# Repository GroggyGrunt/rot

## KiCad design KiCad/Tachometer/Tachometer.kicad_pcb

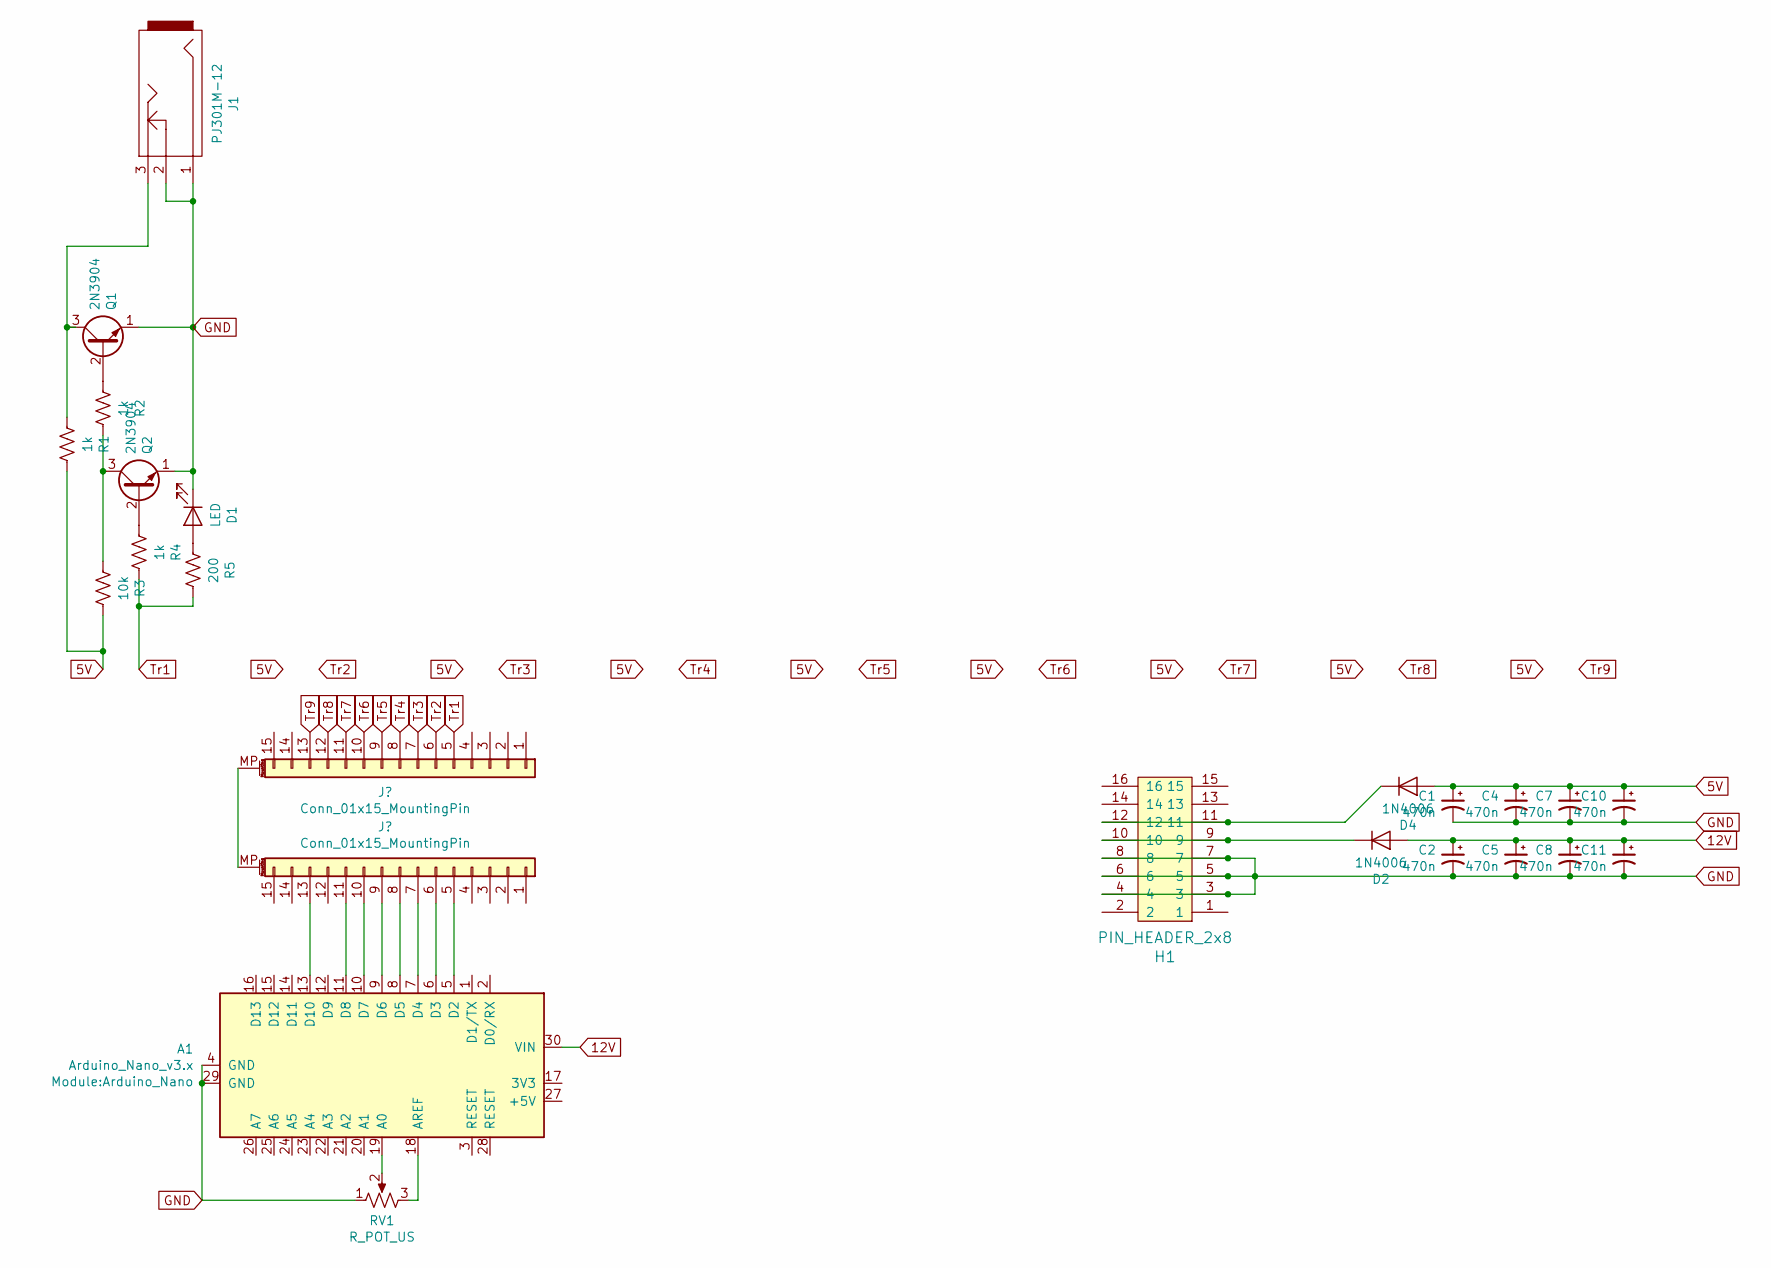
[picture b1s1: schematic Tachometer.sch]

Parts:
A1: Arduino_Nano_v3.x; Arduino_Nano
C1, C2, C4, C5, C7, C8, C10, C11: 470n; C_1206_3216Metric_Pad1.42x1.75mm_HandSolder
D1: LED; LED_D3.0mm_FlatTop
D2, D4: 1N4006; D_DO-41_SOD81_P7.62mm_Horizontal
H1: PIN_HEADER_2x8; PinHeader_2x08_P2.54mm_Vertical
J1: PJ301M-12
Q1, Q2: 2N3904; SOT-23-3
R1, R2, R4: 1k; R_1206_3216Metric_Pad1.42x1.75mm_HandSolder
R3: 10k; R_1206_3216Metric_Pad1.42x1.75mm_HandSolder
R5: 200; R_1206_3216Metric_Pad1.42x1.75mm_HandSolder
RV1: R_POT_US; Alpha9mmPot

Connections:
5V: C1.1, C4.1, C7.1, C10.1, D4.2 (A), R1.1, R3.1
12V: A1.30 (VIN), C2.1, C5.1, C8.1, C11.1, D2.2 (A)
GND: A1.4 (GND), A1.29 (GND), C1.2, C2.2, C4.2, C5.2, C7.2, C8.2, C10.2, C11.2, D1.1 (K), H1.3, H1.4, H1.5, H1.6, H1.7, H1.8, J1.1, J1.2, Q1.1 (E), Q2.1 (E), RV1.1
unnamed 6: A1.5 (D2); also elsewhere on the board
unnamed 7: A1.6 (D3); also elsewhere on the board
unnamed 8: A1.7 (D4); also elsewhere on the board
unnamed 9: A1.8 (D5); also elsewhere on the board
unnamed 10: A1.9 (D6); also elsewhere on the board
unnamed 11: A1.10 (D7); also elsewhere on the board
unnamed 12: A1.11 (D8); also elsewhere on the board
unnamed 14: A1.13 (D10); also elsewhere on the board
unnamed: A1.18 (AREF), RV1.3
unnamed: A1.19 (A0), RV1.2
unnamed: D1.2 (A), R5.2
unnamed: D2.1 (K), H1.9, H1.10
unnamed: D4.1 (K), H1.11, H1.12
unnamed: J1.3, Q1.3 (C), R1.2
unnamed: Q1.2 (B), R2.2
unnamed: Q2.2 (B), R4.2
unnamed: Q2.3 (C), R2.1, R3.2
Tr1: R4.1, R5.1; also elsewhere on the board

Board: 2 copper layers, 24 parts (3 on the bottom side), 21 nets, no tracks yet.

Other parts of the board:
J2, J3: Conn_01x15_MountingPin; PinHeader_1x15_P2.54mm_Vertical

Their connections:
unnamed 6: J3.5; also elsewhere on the board
unnamed 7: J3.6; also elsewhere on the board
unnamed 8: J3.7; also elsewhere on the board
unnamed 9: J3.8; also elsewhere on the board
unnamed 10: J3.9; also elsewhere on the board
unnamed 11: J3.10; also elsewhere on the board
unnamed 12: J3.11; also elsewhere on the board
unnamed 14: J3.13; also elsewhere on the board
Tr1: J2.5; also elsewhere on the board

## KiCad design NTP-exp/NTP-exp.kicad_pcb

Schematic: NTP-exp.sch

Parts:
D1, D3: LED; LED_D3.0mm_FlatTop
D2: CC56-12CGKWA; AFF_2x7SEG-DIGIT_10mm
H1: Expander; PinHeader_2x08_P2.54mm_Vertical
J1, J2, J3, J4, J5, J6, J7, J8, J9, J10, J11, J12, J13, J14: PJ301M-12
R1, R14: 1k; R_0805_2012Metric_Pad1.15x1.40mm_HandSolder
R2, R15: 10m; R_0805_2012Metric_Pad1.15x1.40mm_HandSolder
R3, R4, R5, R6, R11, R12, R13, R16, R17, R18, R19, R20, R21, R22: 51; R_0805_2012Metric_Pad1.15x1.40mm_HandSolder
R7, R8, R9, R10: 200; R_0805_2012Metric_Pad1.15x1.40mm_HandSolder
SW1, SW2: SW_Rotary12
U1, U3, U4, U5: TL074; DIP-14_W7.62mm_Socket
U2: ATmega328P-PU; DIP-28_W7.62mm_Socket

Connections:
5V: H1.15, H1.16, U1.4 (V+), U2.7 (VCC), U2.20 (AVCC), U3.4 (V+), U4.4 (V+), U5.4 (V+)
C1: R7.1, U2.11 (PD5)
C2: R8.1, U2.6 (PD4)
C3: R9.1, U2.5 (PD3)
C4: R10.1, U2.4 (PD2)
GND: H1.13, H1.14, J1.1, J1.2, J2.1, J2.2, J3.1, J3.2, J4.1, J4.2, J5.1, J5.2, J6.1, J6.2, J7.1, J7.2, J8.1, J8.2, J9.1, J9.2, J10.1, J10.2, J11.1, J11.2, J12.1, J12.2, J13.1, J13.2, J14.1, J14.2, R1.2, R2.2, R14.2, R15.2, U1.11 (V-), U2.8 (GND), U2.22 (GND), U3.11 (V-), U4.11 (V-), U5.11 (V-)
La: D2.11 (a), U2.12 (PD6)
Lb: D2.7 (b), U2.13 (PD7)
Lc: D2.4 (c), U2.14 (PB0)
Ld: D2.2 (d), U2.15 (PB1)
Le: D2.1 (e), U2.16 (PB2)
Lf: D2.10 (f), U2.17 (PB3)
Lg: D2.5 (g), U2.18 (PB4)
unnamed: D1.1 (K), R1.1, U1.2 (-)
unnamed: D1.2 (A), U1.1
unnamed: D2.6 (CC4), R10.2
unnamed: D2.8 (CC3), R9.2
unnamed: D2.9 (CC2), R8.2
unnamed: D2.12 (CC1), R7.2
unnamed: D3.1 (K), R14.1, U4.2 (-)
unnamed: D3.2 (A), U4.1
unnamed: J1.3, R3.2
unnamed: J2.3, R4.2
unnamed: J3.3, R5.2
unnamed: J4.3, R6.2
unnamed: J5.3, R11.2
unnamed: J6.3, R12.2
unnamed: J7.3, R13.2
unnamed: J8.3, R16.2
unnamed: J9.3, R17.2
unnamed: J10.3, R18.2
unnamed: J11.3, R19.2
unnamed: J12.3, R20.2
unnamed: J13.3, R21.2
unnamed: J14.3, R22.2
unnamed: R3.1, U1.6 (-), U1.7
unnamed: R4.1, U1.8, U1.9 (-)
unnamed: R5.1, U1.13 (-), U1.14
unnamed: R6.1, U3.1, U3.2 (-)
unnamed: R11.1, U3.6 (-), U3.7
unnamed: R12.1, U3.8, U3.9 (-)
unnamed: R13.1, U3.13 (-), U3.14
unnamed: R16.1, U4.6 (-), U4.7
unnamed: R17.1, U4.8, U4.9 (-)
unnamed: R18.1, U4.13 (-), U4.14
unnamed: R19.1, U5.1, U5.2 (-)
unnamed: R20.1, U5.6 (-), U5.7
unnamed: R21.1, U5.8, U5.9 (-)
unnamed: R22.1, U5.13 (-), U5.14
SDA: H1.11, U2.27 (PC4)
SDC: H1.12, U2.28 (PC5)
STr1: R2.1, R15.1, U1.3 (+), U1.5 (+), U1.10 (+), U1.12 (+), U3.3 (+), U3.5 (+), U3.10 (+), U3.12 (+), U4.3 (+), U4.5 (+), U4.10 (+), U4.12 (+), U5.3 (+), U5.5 (+), U5.10 (+), U5.12 (+)
Tr1: H1.1
Tr2: H1.2
Tr3: H1.3
Tr4: H1.4
Tr5: H1.5
Tr6: H1.6
Tr7: H1.7
Tr8: H1.8
Tr9: H1.9

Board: 2 copper layers, 45 parts (0 on the bottom side), 52 nets, no tracks yet.

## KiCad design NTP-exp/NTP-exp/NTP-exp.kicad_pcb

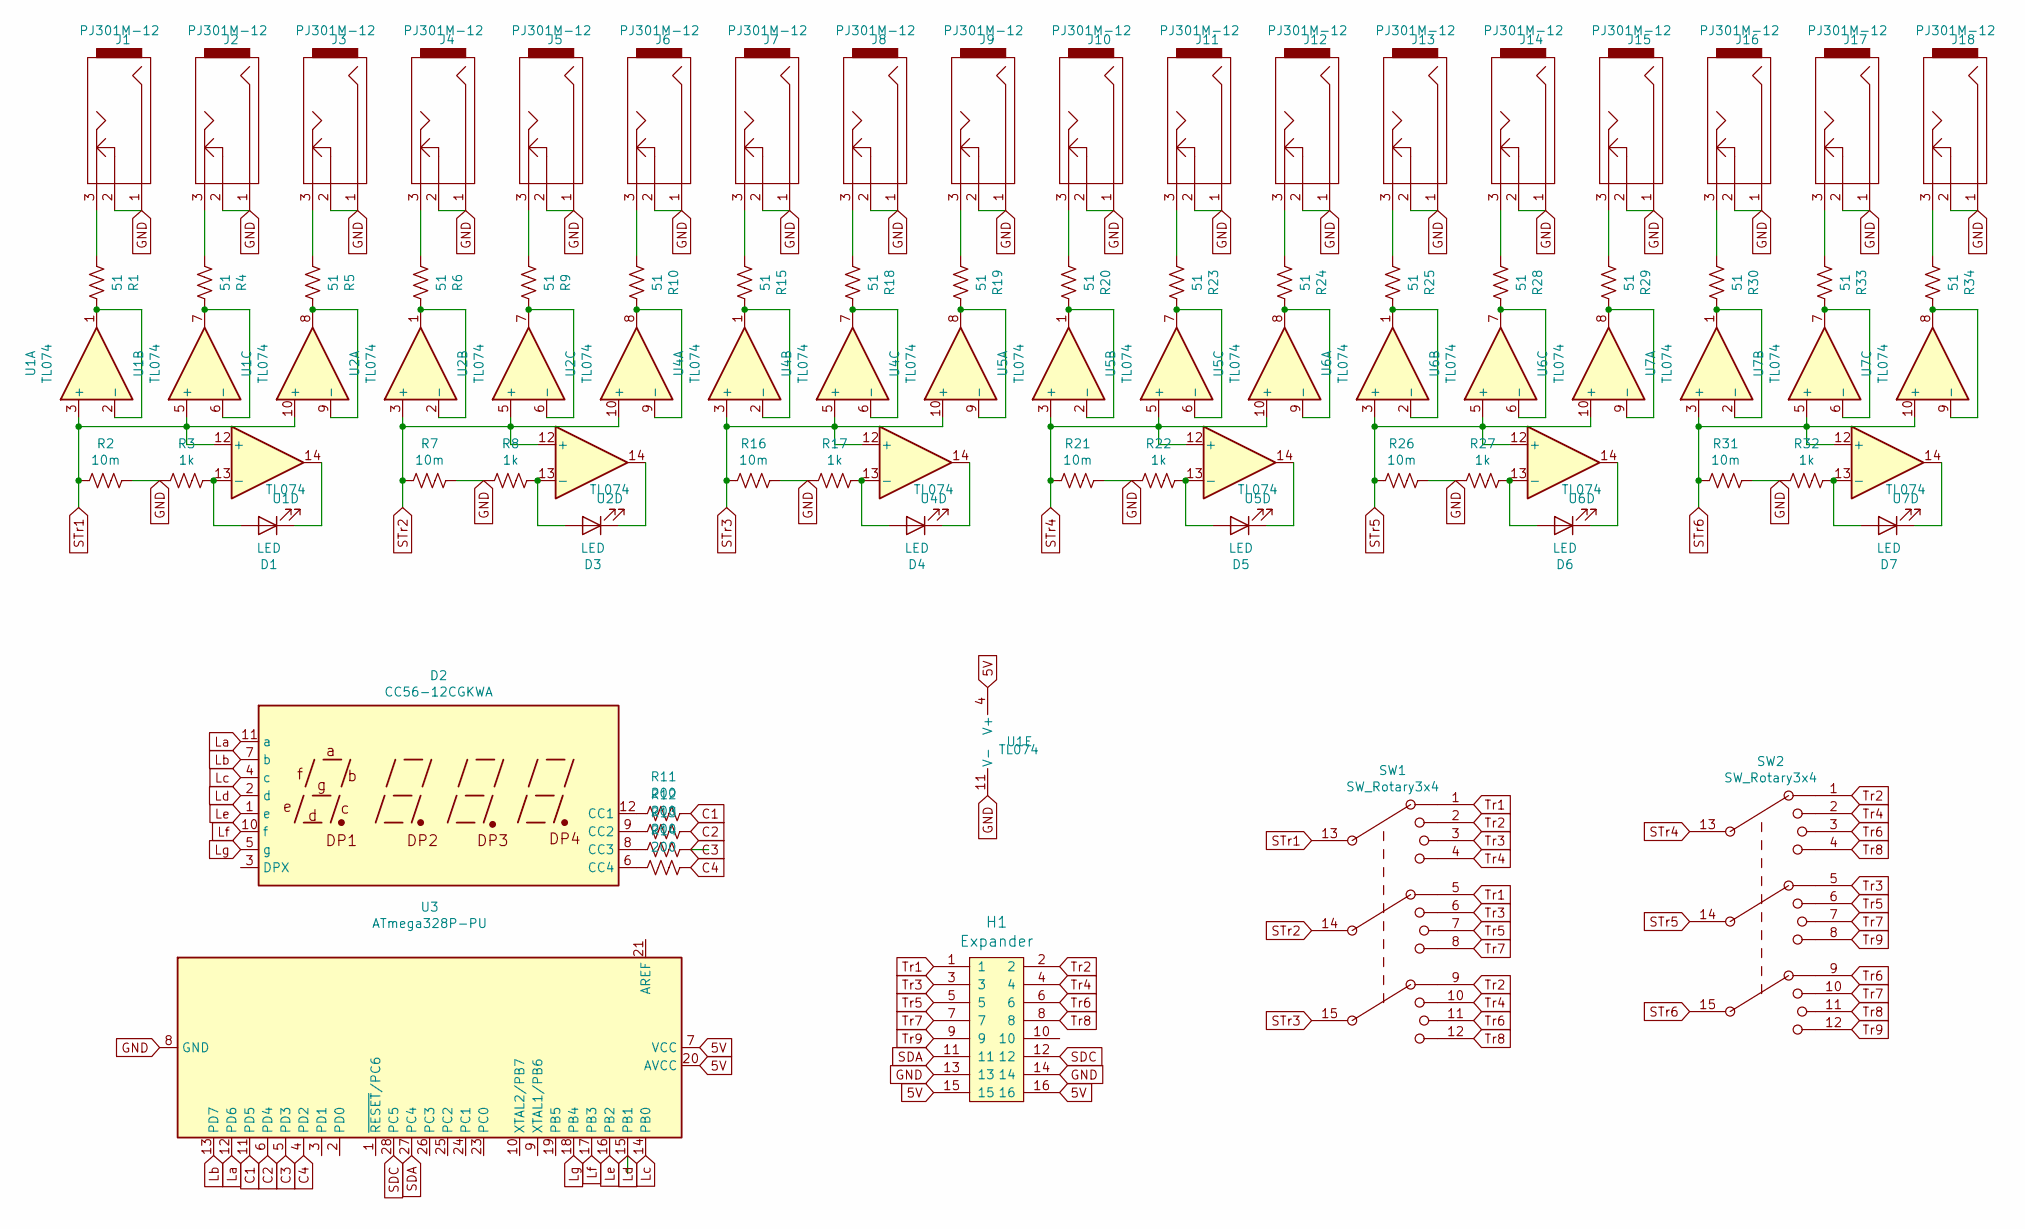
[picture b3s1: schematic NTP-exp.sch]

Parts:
D1, D3, D4, D5, D6, D7: LED; LED_D3.0mm_FlatTop
D2: CC56-12CGKWA; AFF_2x7SEG-DIGIT_10mm
H1: Expander; PinHeader_2x08_P2.54mm_Vertical
J1, J2, J3, J4, J5, J6, J7, J8, J9, J10, J11, J12, J13, J14, J15, J16, J17, J18: PJ301M-12
R1, R4, R5, R6, R9, R10, R15, R18, R19, R20, R23, R24, R25, R28, R29, R30, R33, R34: 51; R_0805_2012Metric_Pad1.15x1.40mm_HandSolder
R2, R7, R16, R21, R26, R31: 10m; R_0805_2012Metric_Pad1.15x1.40mm_HandSolder
R3, R8, R17, R22, R27, R32: 1k; R_0805_2012Metric_Pad1.15x1.40mm_HandSolder
R11, R12, R13, R14: 200; R_0805_2012Metric_Pad1.15x1.40mm_HandSolder
SW1, SW2: SW_Rotary3x4; Potentiometer_Alpha_RD901F-40-00D_Single_Vertical
U1, U2, U4, U5, U6, U7: TL074; DIP-14_W7.62mm_Socket
U3: ATmega328P-PU; DIP-28_W7.62mm_Socket

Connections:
5V: H1.15, H1.16, U1.4 (V+), U3.7 (VCC), U3.20 (AVCC)
C1: R11.1, U3.11 (PD5)
C2: R12.1, U3.6 (PD4)
C3: R13.1, U3.5 (PD3)
C4: R14.1, U3.4 (PD2)
GND: H1.13, H1.14, J1.1, J1.2, J2.1, J2.2, J3.1, J3.2, J4.1, J4.2, J5.1, J5.2, J6.1, J6.2, J7.1, J7.2, J8.1, J8.2, J9.1, J9.2, J10.1, J10.2, J11.1, J11.2, J12.1, J12.2, J13.1, J13.2, J14.1, J14.2, J15.1, J15.2, J16.1, J16.2, J17.1, J17.2, J18.1, J18.2, R2.1, R3.2, R7.1, R8.2, R16.1, R17.2, R21.1, R22.2, R26.1, R27.2, R31.1, R32.2, U1.11 (V-), U3.8 (GND), U3.22 (GND)
La: D2.11 (a), U3.12 (PD6)
Lb: D2.7 (b), U3.13 (PD7)
Lc: D2.4 (c), U3.14 (PB0)
Ld: D2.2 (d), U3.15 (PB1)
Le: D2.1 (e), U3.16 (PB2)
Lf: D2.10 (f), U3.17 (PB3)
Lg: D2.5 (g), U3.18 (PB4)
unnamed: D1.1 (K), U1.14
unnamed: D1.2 (A), R3.1, U1.13 (-)
unnamed: D2.6 (CC4), R14.2
unnamed: D2.8 (CC3), R13.2
unnamed: D2.9 (CC2), R12.2
unnamed: D2.12 (CC1), R11.2
unnamed: D3.1 (K), U2.14
unnamed: D3.2 (A), R8.1, U2.13 (-)
unnamed: D4.1 (K), U4.14
unnamed: D4.2 (A), R17.1, U4.13 (-)
unnamed: D5.1 (K), U5.14
unnamed: D5.2 (A), R22.1, U5.13 (-)
unnamed: D6.1 (K), U6.14
unnamed: D6.2 (A), R27.1, U6.13 (-)
unnamed: D7.1 (K), U7.14
unnamed: D7.2 (A), R32.1, U7.13 (-)
unnamed: J1.3, R1.2
unnamed: J2.3, R4.2
unnamed: J3.3, R5.2
unnamed: J4.3, R6.2
unnamed: J5.3, R9.2
unnamed: J6.3, R10.2
unnamed: J7.3, R15.2
unnamed: J8.3, R18.2
unnamed: J9.3, R19.2
unnamed: J10.3, R20.2
unnamed: J11.3, R23.2
unnamed: J12.3, R24.2
unnamed: J13.3, R25.2
unnamed: J14.3, R28.2
unnamed: J15.3, R29.2
unnamed: J16.3, R30.2
unnamed: J17.3, R33.2
unnamed: J18.3, R34.2
unnamed: R1.1, U1.1, U1.2 (-)
unnamed: R4.1, U1.6 (-), U1.7
unnamed: R5.1, U1.8, U1.9 (-)
unnamed: R6.1, U2.1, U2.2 (-)
unnamed: R9.1, U2.6 (-), U2.7
unnamed: R10.1, U2.8, U2.9 (-)
unnamed: R15.1, U4.1, U4.2 (-)
unnamed: R18.1, U4.6 (-), U4.7
unnamed: R19.1, U4.8, U4.9 (-)
unnamed: R20.1, U5.1, U5.2 (-)
unnamed: R23.1, U5.6 (-), U5.7
unnamed: R24.1, U5.8, U5.9 (-)
unnamed: R25.1, U6.1, U6.2 (-)
unnamed: R28.1, U6.6 (-), U6.7
unnamed: R29.1, U6.8, U6.9 (-)
unnamed: R30.1, U7.1, U7.2 (-)
unnamed: R33.1, U7.6 (-), U7.7
unnamed: R34.1, U7.8, U7.9 (-)
SDA: H1.11, U3.27 (PC4)
SDC: H1.12, U3.28 (PC5)
STr1: R2.2, SW1.13, U1.3 (+), U1.5 (+), U1.10 (+), U1.12 (+)
STr2: R7.2, SW1.14, U2.3 (+), U2.5 (+), U2.10 (+), U2.12 (+)
STr3: R16.2, SW1.15, U4.3 (+), U4.5 (+), U4.10 (+), U4.12 (+)
STr4: R21.2, SW2.13, U5.3 (+), U5.5 (+), U5.10 (+), U5.12 (+)
STr5: R26.2, SW2.14, U6.3 (+), U6.5 (+), U6.10 (+), U6.12 (+)
STr6: R31.2, SW2.15, U7.3 (+), U7.5 (+), U7.10 (+), U7.12 (+)
Tr1: H1.1, SW1.1, SW1.5
Tr2: H1.2, SW1.2, SW1.9, SW2.1
Tr3: H1.3, SW1.3, SW1.6, SW2.5
Tr4: H1.4, SW1.4, SW1.10, SW2.2
Tr5: H1.5, SW1.7, SW2.6
Tr6: H1.6, SW1.11, SW2.3, SW2.9
Tr7: H1.7, SW1.8, SW2.7, SW2.10
Tr8: H1.8, SW1.12, SW2.4, SW2.11
Tr9: H1.9, SW2.8, SW2.12

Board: 2 copper layers, 67 parts (5 on the bottom side), 73 nets, no tracks yet.

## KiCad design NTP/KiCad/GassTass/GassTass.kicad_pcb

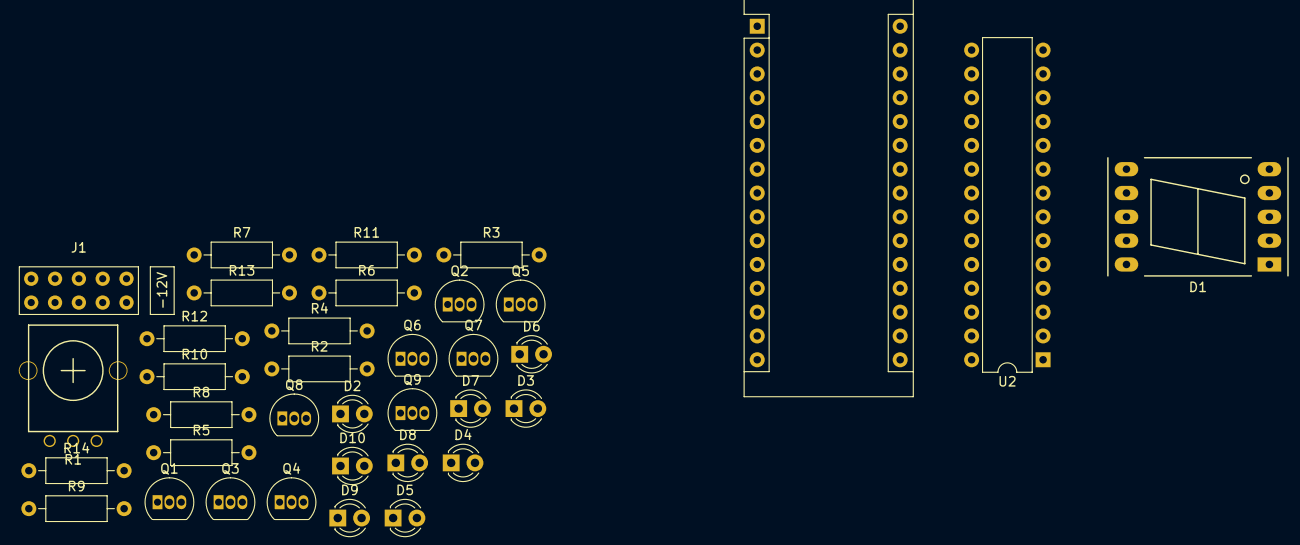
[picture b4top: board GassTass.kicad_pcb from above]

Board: 2 copper layers, 36 parts (0 on the bottom side), 39 nets, no tracks yet.

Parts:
D1: CC56-12CGKWA; 7SegmentLED_LTS6760_LTS6780
D2, D3, D4, D5, D6, D7, D8, D9, D10: LED; LED_D3.0mm_FlatTop
J1: EURO_PWR_2x5; europwr2x5
Q1, Q2, Q3, Q4, Q5, Q6, Q7, Q8, Q9: 2N3904; TO-92_Inline
R1: R_POT_US; Alpha9mmPot
R2, R3, R4, R5, R6, R7, R8, R9, R10, R11, R12, R13, R14: R_US; R_Axial_DIN0207_L6.3mm_D2.5mm_P10.16mm_Horizontal
U1: Arduino_Nano_v3.x; Arduino_Nano
U2: ATmega328P-PU; DIP-28_W7.62mm

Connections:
+12V: J1.1, J1.2, Q1.3, Q2.3, Q3.3, Q4.3, Q5.3, Q6.3, Q7.3, Q8.3, Q9.3
-12V: J1.9, J1.10
GND: J1.3, J1.4, J1.5, J1.6, J1.7, J1.8, R1.1, R2.1, R7.1, R8.1, R9.1, R10.1, R11.1, R12.1, R13.1, R14.1, U1.4, U1.29, U2.8, U2.22
unnamed: D1.1, U2.16
unnamed: D1.2, U2.15
unnamed: D1.4, U2.14
unnamed: D1.5, U2.18
unnamed: D1.6, R3.1
unnamed: D1.7, U2.13
unnamed: D1.8, R4.1
unnamed: D1.9, R5.1
unnamed: D1.10, U2.17
unnamed: D2.1, R2.2
unnamed: D2.2, Q1.2, U1.5
unnamed: D3.1, R7.2
unnamed: D3.2, Q2.2, U1.6
unnamed: D4.1, R8.2
unnamed: D4.2, Q3.2, U1.7
unnamed: D5.1, R9.2
unnamed: D5.2, Q4.2, U1.8
unnamed: D6.1, R10.2
unnamed: D6.2, Q5.2, U1.9
unnamed: D7.1, R11.2
unnamed: D7.2, Q6.2, U1.10
unnamed: D8.1, R12.2
unnamed: D8.2, Q7.2, U1.11
unnamed: D9.1, R13.2
unnamed: D9.2, Q8.2, U1.12
unnamed: D10.1, R14.2
unnamed: D10.2, Q9.2, U1.13
unnamed: R1.2, U1.19
unnamed: R1.3, U1.18
unnamed: R3.2, U2.4
unnamed: R4.2, U2.5
unnamed: R5.2, U2.6
unnamed: R6.2, U2.11
unnamed: U1.23, U2.27
unnamed: U1.24, U2.28
unnamed: U1.27, U2.7

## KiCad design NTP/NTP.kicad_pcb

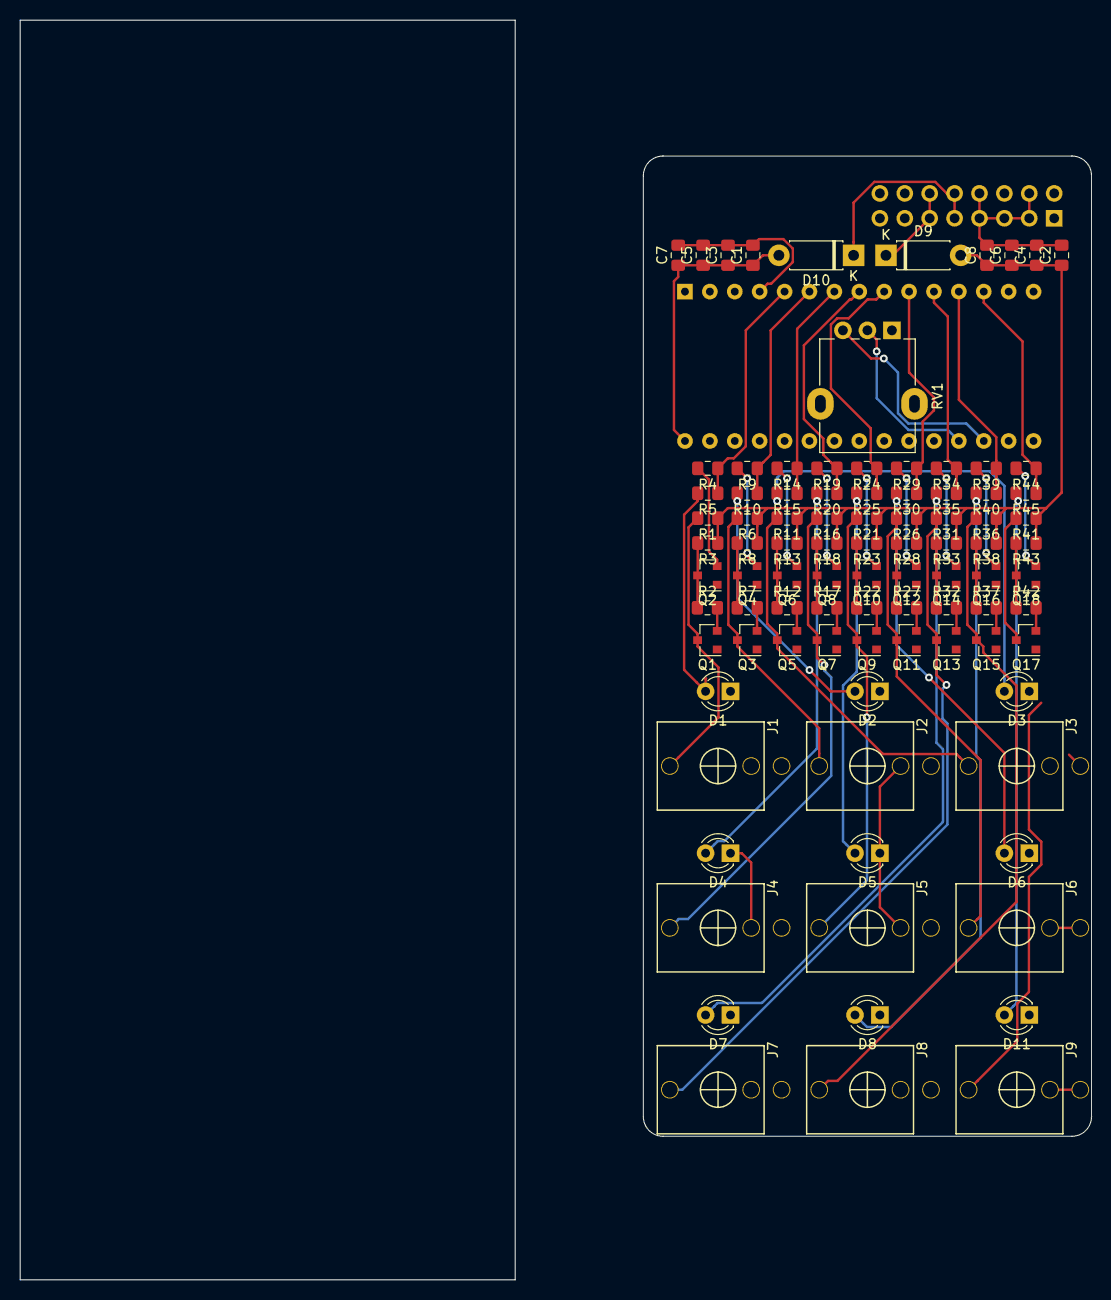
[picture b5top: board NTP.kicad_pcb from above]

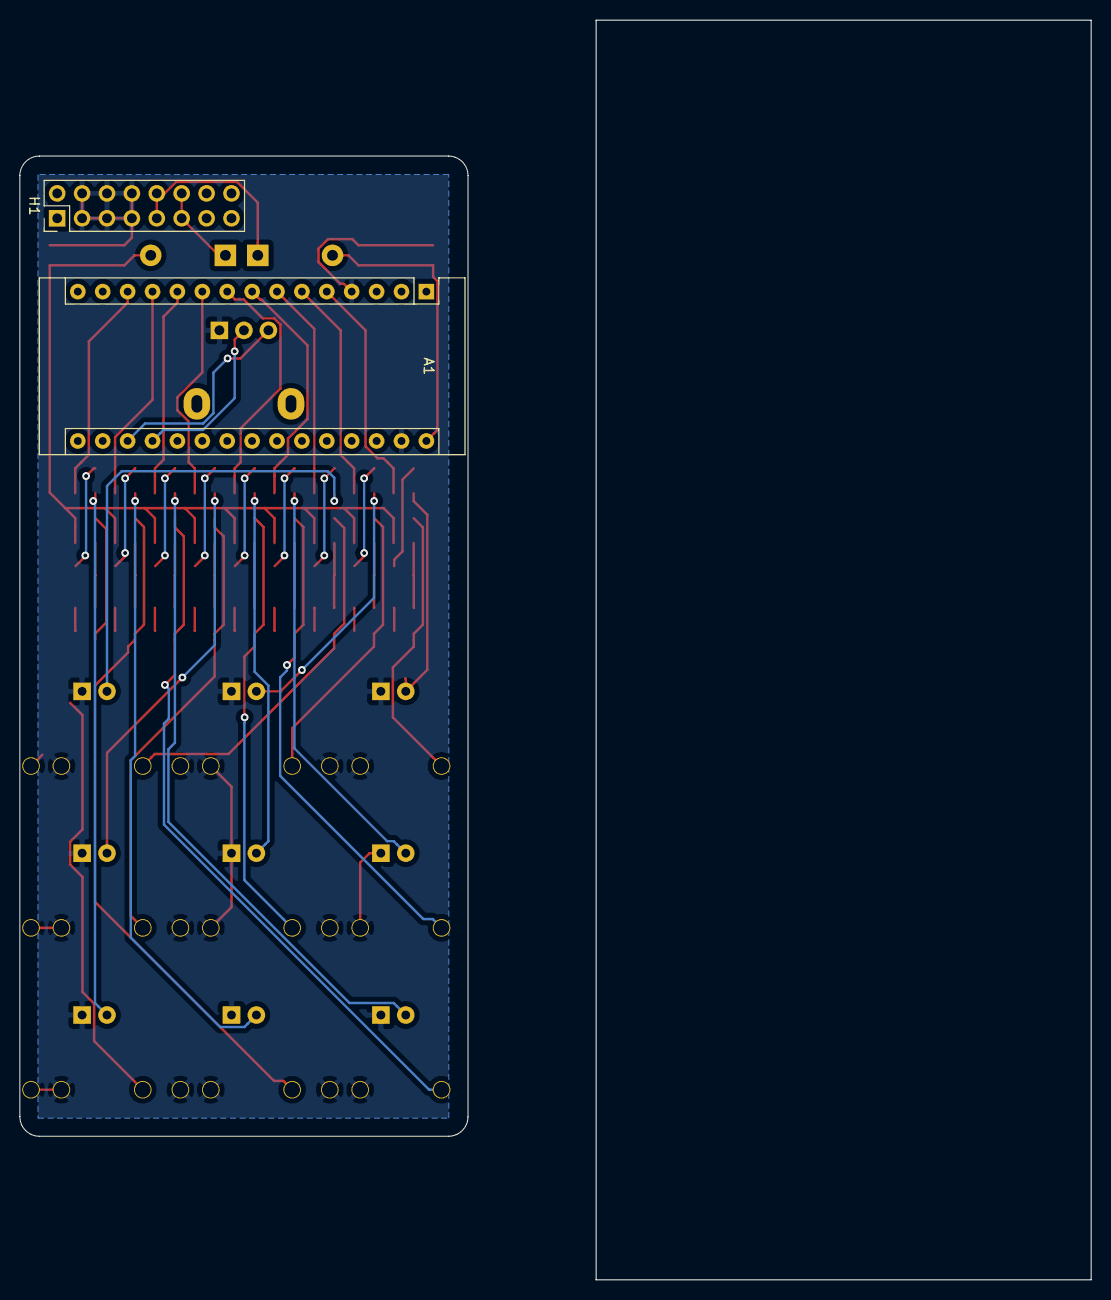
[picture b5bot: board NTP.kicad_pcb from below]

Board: 2 copper layers, 45.7 x 100.0 mm, 94 parts (2 on the bottom side), 61 nets.

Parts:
A1: Arduino_Nano_v3.x; Arduino_Nano
C1, C2, C3, C4, C5, C6, C7, C8: 470n; C_0805_2012Metric_Pad1.15x1.40mm_HandSolder
D1, D2, D3, D4, D5, D6, D7, D8, D11: LED; LED_D3.0mm_FlatTop
D9, D10: 1N4006; D_DO-41_SOD81_P7.62mm_Horizontal
H1: PIN_HEADER_2x8; PinHeader_2x08_P2.54mm_Vertical
J1, J2, J3, J4, J5, J6, J7, J8, J9: PJ301M-12
Q1, Q2, Q3, Q4, Q5, Q6, Q7, Q8, Q9, Q10, Q11, Q12, Q13, Q14, Q15, Q16, Q17, Q18: 2N3904; SOT-23
R1, R2, R4, R6, R7, R9, R11, R12, R14, R16, R17, R19, R21, R22, R24, R26, R27, R29, R31, R32, R34, R36, R37, R39, R41, R42, R44: 1k; R_0805_2012Metric_Pad1.15x1.40mm_HandSolder
R3, R8, R13, R18, R23, R28, R33, R38, R43: 10k; R_0805_2012Metric_Pad1.15x1.40mm_HandSolder
R5, R10, R15, R20, R25, R30, R35, R40, R45: 200; R_0805_2012Metric_Pad1.15x1.40mm_HandSolder
RV1: R_POT_US; Potentiometer_Alpha_RD901F-40-00D_Single_Vertical

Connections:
5V: C2.1, C4.1, C6.1, C8.1, D9.2, R1.1, R3.1, R6.1, R8.1, R11.1, R13.1, R16.1, R18.1, R21.1, R23.1, R26.1, R28.1, R31.1, R33.1, R36.1, R38.1, R41.1, R43.1
12V: A1.30, C1.1, C3.1, C5.1, C7.1, D10.2
GND: A1.4, A1.29, C1.2, C2.2, C3.2, C4.2, C5.2, C6.2, C7.2, C8.2, D1.1, D2.1, D3.1, D4.1, D5.1, D6.1, D7.1, D8.1, D11.1, H1.3, H1.4, H1.5, H1.6, H1.7, H1.8, J1.1, J1.2, J2.1, J2.2, J3.1, J3.2, J4.1, J4.2, J5.1, J5.2, J6.1, J6.2, J7.1, J7.2, J8.1, J8.2, J9.1, J9.2, Q1.1, Q2.1, Q3.1, Q4.1, Q5.1, Q6.1, Q7.1, Q8.1, Q9.1, Q10.1, Q11.1, Q12.1, Q13.1, Q14.1, Q15.1, Q16.1, Q17.1, Q18.1, RV1.1
unnamed: A1.18, RV1.3
unnamed: A1.19, RV1.2
unnamed: D1.2, R5.2
unnamed: D2.2, R10.2
unnamed: D3.2, R15.2
unnamed: D4.2, R20.2
unnamed: D5.2, R25.2
unnamed: D6.2, R30.2
unnamed: D7.2, R35.2
unnamed: D8.2, R40.2
unnamed: D9.1, H1.11, H1.12
unnamed: D10.1, H1.9, H1.10
unnamed: D11.2, R45.2
unnamed: J1.3, Q1.3, R1.2
unnamed: J2.3, Q3.3, R6.2
unnamed: J3.3, Q5.3, R11.2
unnamed: J4.3, Q7.3, R16.2
unnamed: J5.3, Q9.3, R21.2
unnamed: J6.3, Q11.3, R26.2
unnamed: J7.3, Q13.3, R31.2
unnamed: J8.3, Q15.3, R36.2
unnamed: J9.3, Q17.3, R41.2
unnamed: Q1.2, R2.2
unnamed: Q2.2, R4.2
unnamed: Q2.3, R2.1, R3.2
unnamed: Q3.2, R7.2
unnamed: Q4.2, R9.2
unnamed: Q4.3, R7.1, R8.2
unnamed: Q5.2, R12.2
unnamed: Q6.2, R14.2
unnamed: Q6.3, R12.1, R13.2
unnamed: Q7.2, R17.2
unnamed: Q8.2, R19.2
unnamed: Q8.3, R17.1, R18.2
unnamed: Q9.2, R22.2
unnamed: Q10.2, R24.2
unnamed: Q10.3, R22.1, R23.2
unnamed: Q11.2, R27.2
unnamed: Q12.2, R29.2
unnamed: Q12.3, R27.1, R28.2
unnamed: Q13.2, R32.2
unnamed: Q14.2, R34.2
unnamed: Q14.3, R32.1, R33.2
unnamed: Q15.2, R37.2
unnamed: Q16.2, R39.2
unnamed: Q16.3, R37.1, R38.2
unnamed: Q17.2, R42.2
unnamed: Q18.2, R44.2
unnamed: Q18.3, R42.1, R43.2
Tr1: A1.5, R4.1, R5.1
Tr2: A1.6, R9.1, R10.1
Tr3: A1.7, R14.1, R15.1
Tr4: A1.8, R19.1, R20.1
Tr5: A1.9, R24.1, R25.1
Tr6: A1.10, R29.1, R30.1
Tr7: A1.11, R34.1, R35.1
Tr8: A1.12, R39.1, R40.1
Tr9: A1.13, R44.1, R45.1

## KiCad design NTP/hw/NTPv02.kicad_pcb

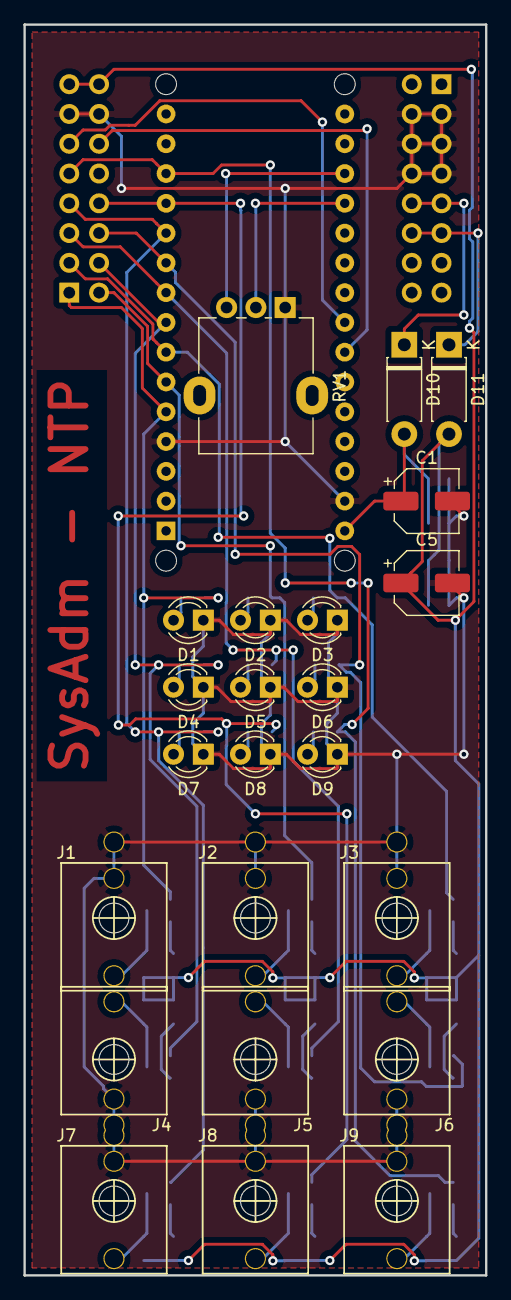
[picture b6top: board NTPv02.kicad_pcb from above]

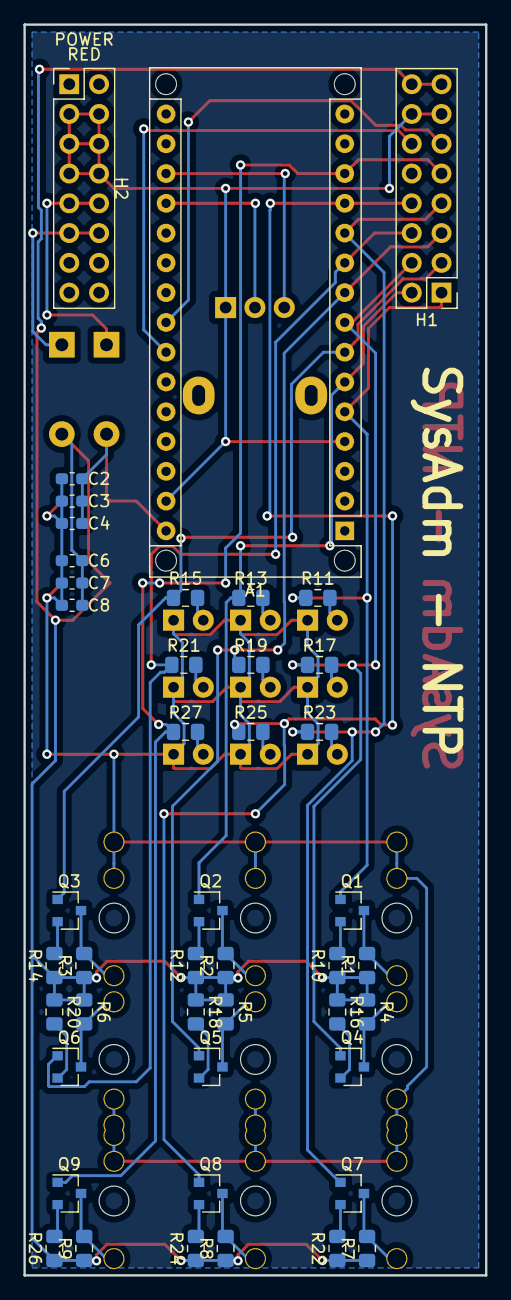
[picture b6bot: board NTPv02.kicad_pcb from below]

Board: 2 copper layers, 39.4 x 106.7 mm, 68 parts (45 on the bottom side), 45 nets.

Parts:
A1: Arduino_Nano_v3.x; Arduino_Nano_WithMountingHoles
C1, C5: 470n; CP_Elec_5x5.3
C2, C3, C4, C6, C7, C8: 22n; C_0603_1608Metric_Pad1.05x0.95mm_HandSolder
D1, D2, D3, D4, D5, D6, D7, D8, D9: LED; LED_D3.0mm_FlatTop
D10, D11: 1N4006; D_DO-41_SOD81_P7.62mm_Horizontal
H1: Expander; PinHeader_2x08_P2.54mm_Vertical
H2: POWER; PinHeader_2x08_P2.54mm_Vertical
J1, J2, J3, J4, J5, J6, J7, J8, J9: PJ301M-12
Q1, Q2, Q3, Q4, Q5, Q6, Q7, Q8, Q9: 2N3904; SOT-23
R1, R2, R3, R4, R5, R6, R7, R8, R9: 6.8k; R_0805_2012Metric_Pad1.15x1.40mm_HandSolder
R10, R12, R14, R16, R18, R20, R22, R24, R26: 2.2k; R_0805_2012Metric_Pad1.15x1.40mm_HandSolder
R11, R13, R15, R17, R19, R21, R23, R25, R27: 200; R_0805_2012Metric_Pad1.15x1.40mm_HandSolder
RV1: R_POT_US; Potentiometer_Alpha_RD901F-40-00D_Single_Vertical

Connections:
5V: C5.1, C6.1, C7.1, C8.1, D11.2, H1.15, H1.16, R1.1, R2.1, R3.1, R4.1, R5.1, R6.1, R7.1, R8.1, R9.1, R10.1, R12.1, R14.1, R16.1, R18.1, R20.1, R22.1, R24.1, R26.1
12V: A1.30, C1.1, C2.1, C3.1, C4.1, D10.2
GND: A1.4, A1.29, C1.2, C2.2, C3.2, C4.2, C5.2, C6.2, C7.2, C8.2, D1.1, D2.1, D3.1, D4.1, D5.1, D6.1, D7.1, D8.1, D9.1, H1.13, H1.14, H2.3, H2.4, H2.5, H2.6, H2.7, H2.8, J1.1, J1.2, J2.1, J2.2, J3.1, J3.2, J4.1, J4.2, J5.1, J5.2, J6.1, J6.2, J7.1, J7.2, J8.1, J8.2, J9.1, J9.2, RV1.1
unnamed: A1.18, RV1.3
unnamed: A1.19, RV1.2
unnamed: D1.2, R11.2
unnamed: D2.2, R13.2
unnamed: D3.2, R15.2
unnamed: D4.2, R17.2
unnamed: D5.2, R19.2
unnamed: D6.2, R21.2
unnamed: D7.2, R23.2
unnamed: D8.2, R25.2
unnamed: D9.2, R27.2
unnamed: D10.1, H2.9, H2.10
unnamed: D11.1, H2.11, H2.12
unnamed: J1.3, Q1.3, R1.2
unnamed: J2.3, Q2.3, R2.2
unnamed: J3.3, Q3.3, R3.2
unnamed: J4.3, Q4.3, R4.2
unnamed: J5.3, Q5.3, R5.2
unnamed: J6.3, Q6.3, R6.2
unnamed: J7.3, Q7.3, R7.2
unnamed: J8.3, Q8.3, R8.2
unnamed: J9.3, Q9.3, R9.2
unnamed: Q1.2, R10.2
unnamed: Q2.2, R12.2
unnamed: Q3.2, R14.2
unnamed: Q4.2, R16.2
unnamed: Q5.2, R18.2
unnamed: Q6.2, R20.2
unnamed: Q7.2, R22.2
unnamed: Q8.2, R24.2
unnamed: Q9.2, R26.2
SDA: A1.23, H1.11
SDC: A1.24, H1.12
Tr1: A1.5, H1.1, Q1.1, R11.1
Tr2: A1.6, H1.2, Q2.1, R13.1
Tr3: A1.7, H1.3, Q3.1, R15.1
Tr4: A1.8, H1.4, Q4.1, R17.1
Tr5: A1.9, H1.5, Q5.1, R19.1
Tr6: A1.10, H1.6, Q6.1, R21.1
Tr7: A1.11, H1.7, Q7.1, R23.1
Tr8: A1.12, H1.8, Q8.1, R25.1
Tr9: A1.13, H1.9, Q9.1, R27.1
